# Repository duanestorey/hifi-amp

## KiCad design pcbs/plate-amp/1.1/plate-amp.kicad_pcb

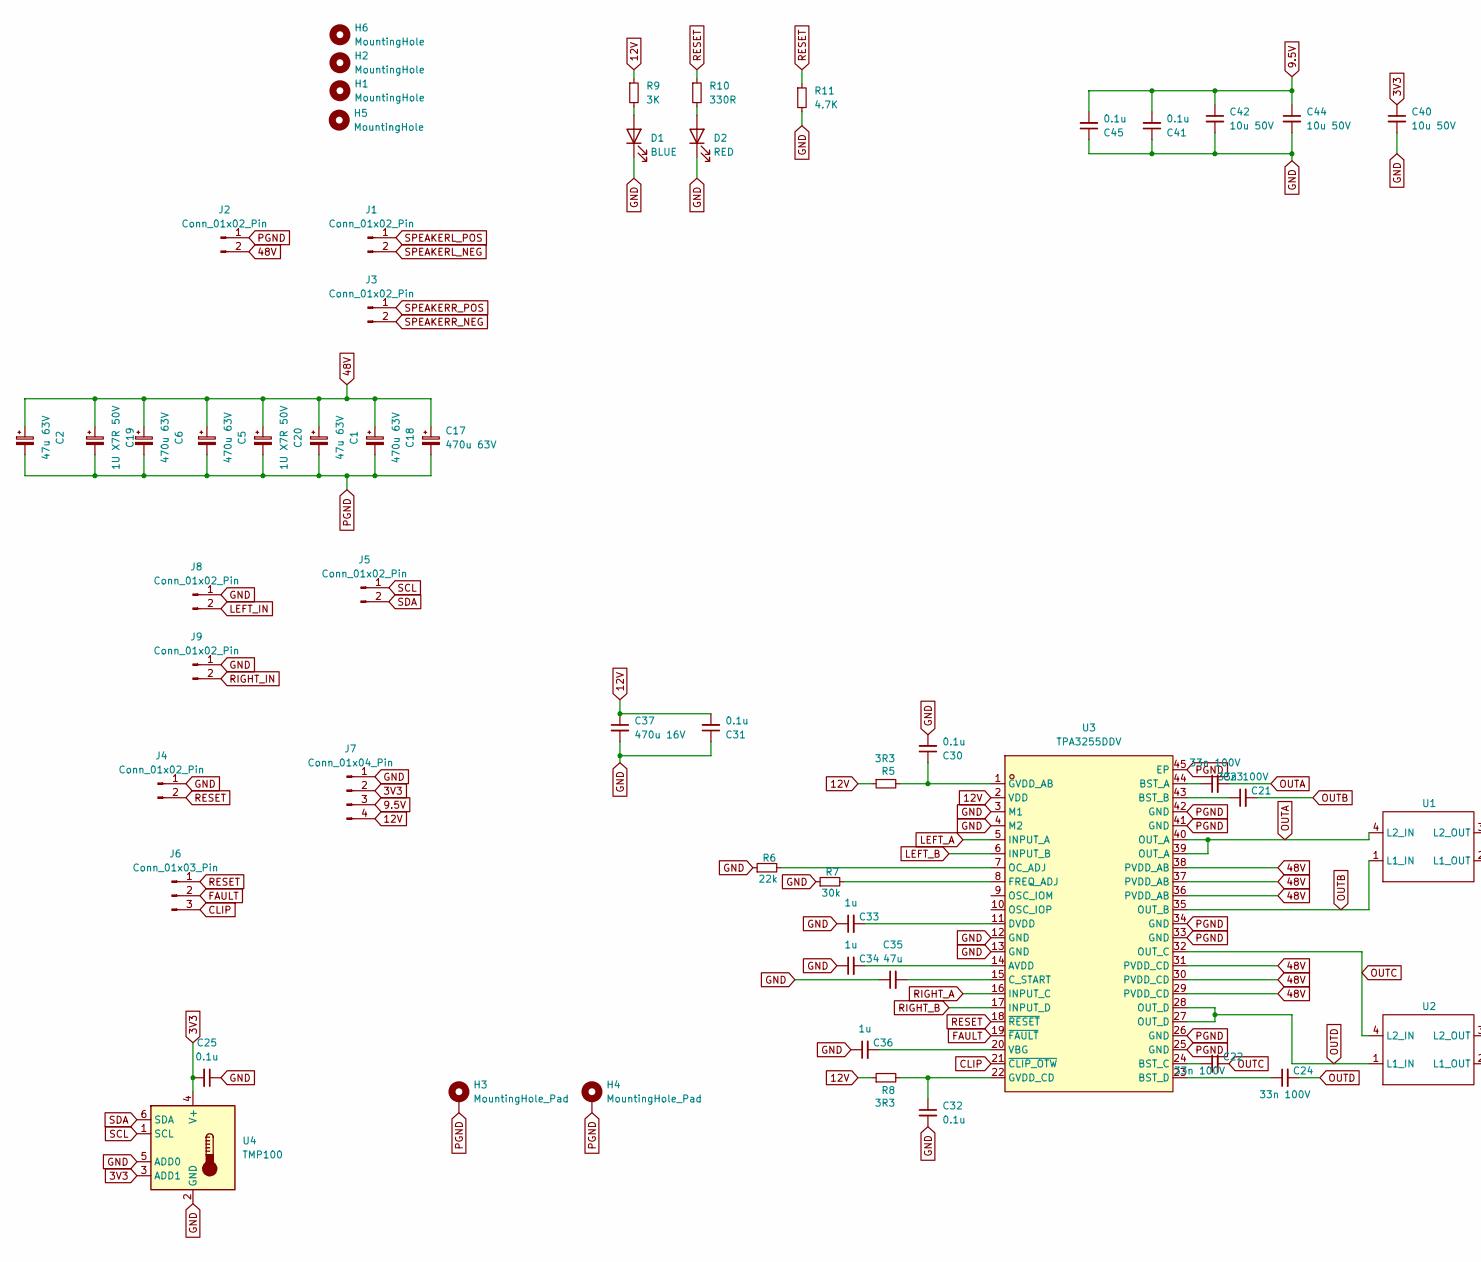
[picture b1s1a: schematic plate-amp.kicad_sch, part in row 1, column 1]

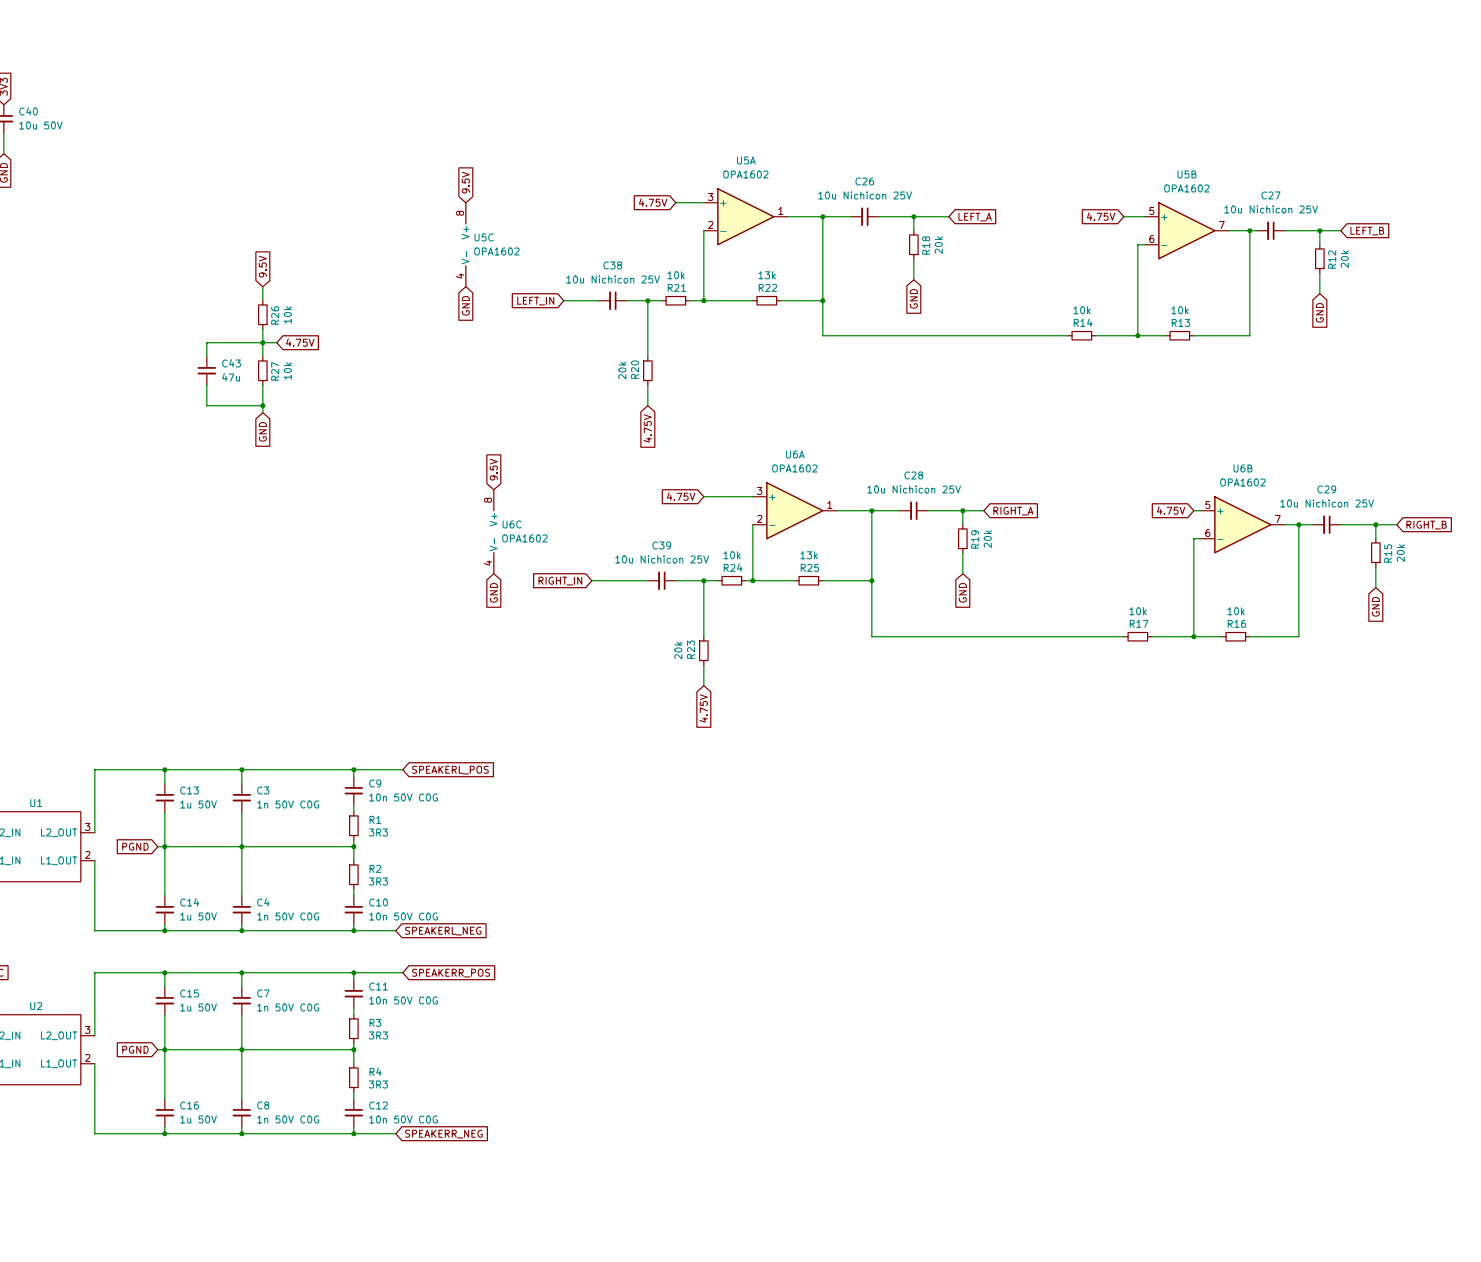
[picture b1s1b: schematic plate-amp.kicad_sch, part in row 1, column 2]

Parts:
C1, C2: 47u 63V; CP_Radial_D6.3mm_P2.50mm; LCSC C45673
C3, C4, C7, C8: 1n 50V C0G; C_1206_3216Metric_Pad1.33x1.80mm_HandSolder
C5, C6, C17, C18: 470u 63V; CP_Radial_D13.0mm_P5.00mm; LCSC C18823
C9, C10, C11, C12: 10n 50V C0G; C_1206_3216Metric_Pad1.33x1.80mm_HandSolder
C13, C14, C15, C16: 1u 50V; CP_Radial_D5.0mm_P2.00mm
C19, C20: 1U X7R 50V; C_1206_3216Metric_Pad1.33x1.80mm_HandSolder; Mouser 80-C1206X475J5RACTU
C21, C22, C23, C24: 33n 100V; C_1206_3216Metric_Pad1.33x1.80mm_HandSolder
C25, C30, C31, C32, C41, C45: 0.1u; C_0805_2012Metric_Pad1.18x1.45mm_HandSolder
C26, C27, C28, C29, C38, C39: 10u Nichicon 25V; CP_Radial_D5.0mm_P2.50mm
C33, C34, C36: 1u; C_1206_3216Metric_Pad1.33x1.80mm_HandSolder
C35, C43: 47u; C_1206_3216Metric_Pad1.33x1.80mm_HandSolder
C37: 470u 16V; CP_Radial_D8.0mm_P3.50mm
C40, C42, C44: 10u 50V; C_1206_3216Metric_Pad1.33x1.80mm_HandSolder
D1: BLUE; LED_0603_1608Metric_Pad1.05x0.95mm_HandSolder; LCSC XL-1608UBC-04
D2: RED; LED_0603_1608Metric_Pad1.05x0.95mm_HandSolder; LCSC XL-1608UBC-04
H1, H2, H5, H6: MountingHole; MountingHole_3.2mm_M3_DIN965_Pad_TopOnly
H3, H4: MountingHole_Pad; MountingHole_3.2mm_M3_DIN965_Pad_TopBottom
J1, J2, J3: Conn_01x02_Pin; TerminalBlock_MaiXu_MX126-5.0-02P_1x02_P5.00mm
J4, J5, J8, J9: Conn_01x02_Pin; JST_PH_B2B-PH-K_1x02_P2.00mm_Vertical
J6: Conn_01x03_Pin; JST_PH_B3B-PH-K_1x03_P2.00mm_Vertical
J7: Conn_01x04_Pin; JST_PH_B4B-PH-K_1x04_P2.00mm_Vertical
R1, R2, R3, R4: 3R3; R_2512_6332Metric_Pad1.40x3.35mm_HandSolder
R5, R8: 3R3; C_0603_1608Metric_Pad1.08x0.95mm_HandSolder
R6: 22k; C_0603_1608Metric_Pad1.08x0.95mm_HandSolder
R7: 30k; C_0603_1608Metric_Pad1.08x0.95mm_HandSolder
R9: 3K; R_0603_1608Metric_Pad0.98x0.95mm_HandSolder
R10: 330R; R_0603_1608Metric_Pad0.98x0.95mm_HandSolder
R11: 4.7K; R_0603_1608Metric_Pad0.98x0.95mm_HandSolder
R12, R15, R18, R19, R20, R23: 20k; C_0603_1608Metric_Pad1.08x0.95mm_HandSolder
R13, R14, R16, R17, R21, R24, R26, R27: 10k; C_0603_1608Metric_Pad1.08x0.95mm_HandSolder
R22, R25: 13k; C_0603_1608Metric_Pad1.08x0.95mm_HandSolder
U1, U2: UA8014-AL
U3: TPA3255DDV; HTSSOP-44_L14.0-W6.1-P0.64-LS8.1-BL-EP; LCSC Part C468240
U4: TMP100; SOT-23-6
U5, U6: OPA1602; SOIC-8_3.9x4.9mm_P1.27mm

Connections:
3V3: C25.2, C40.1, J7.2, U4.3 (ADD1), U4.4 (V+)
4.75V: C43.1, R20.2, R23.2, R26.1, R27.2, U5.3 (+), U5.5 (+), U6.3 (+), U6.5 (+)
9.5V: C41.2, C42.1, C44.1, C45.2, J7.3, R26.2, U5.8 (V+), U6.8 (V+)
12V: C31.2, C37.1, J7.4, R5.1, R8.1, R9.1, U3.2 (VDD)
48V: C1.1, C2.1, C5.1, C6.1, C17.1, C18.1, C19.1, C20.1, J2.2, U3.29 (PVDD_CD), U3.30 (PVDD_CD), U3.31 (PVDD_CD), U3.36 (PVDD_AB), U3.37 (PVDD_AB), U3.38 (PVDD_AB)
CLIP: J6.3, U3.21 (~CLIP_OTW)
FAULT: J6.2, U3.19 (~FAULT)
GND: C25.1, C30.2, C31.1, C32.2, C33.1, C34.1, C35.1, C36.1, C37.2, C40.2, C41.1, C42.2, C43.2, C44.2, C45.1, D1.1 (K), D2.1 (K), J4.1, J7.1, J8.1, J9.1, R6.1, R7.1, R11.2, R12.1, R15.1, R18.1, R19.1, R27.1, U3.3 (M1), U3.4 (M2), U3.12 (GND), U3.13 (GND), U4.2 (GND), U4.5 (ADD0), U5.4 (V-), U6.4 (V-)
LEFT_A: C26.1, R18.2, U3.5 (INPUT_A)
LEFT_B: C27.1, R12.2, U3.6 (INPUT_B)
LEFT_IN: C38.2, J8.2
unnamed: C9.2, R1.1
unnamed: C10.1, R2.2
unnamed: C11.2, R3.1
unnamed: C12.1, R4.2
unnamed: C26.2, R14.2, R22.1, U5.1
unnamed: C27.2, R13.1, U5.7
unnamed: C28.2, R17.2, R25.1, U6.1
unnamed: C29.2, R16.1, U6.7
unnamed: C38.1, R20.1, R21.2
unnamed: C39.1, R23.1, R24.2
unnamed: D1.2 (A), R9.2
unnamed: D2.2 (A), R10.2
unnamed: C34.2, U3.14 (AVDD)
unnamed: C23.1, U3.44 (BST_A)
unnamed: C21.1, U3.43 (BST_B)
unnamed: C22.1, U3.24 (BST_C)
unnamed: C24.1, U3.23 (BST_D)
unnamed: C35.2, U3.15 (C_START)
unnamed: C33.2, U3.11 (DVDD)
unnamed: R7.2, U3.8 (FREQ_ADJ)
unnamed: C30.1, R5.2, U3.1 (GVDD_AB)
unnamed: C32.1, R8.2, U3.22 (GVDD_CD)
unnamed: R6.2, U3.7 (OC_ADJ)
unnamed: C36.2, U3.20 (VBG)
unnamed: R21.1, R22.2, U5.2 (-)
unnamed: R13.2, R14.1, U5.6 (-)
unnamed: R24.1, R25.2, U6.2 (-)
unnamed: R16.2, R17.1, U6.6 (-)
OUTA: C23.2, U1.4 (L2_IN), U3.39 (OUT_A), U3.40 (OUT_A)
OUTB: C21.2, U1.1 (L1_IN), U3.35 (OUT_B)
OUTC: C22.2, U2.4 (L2_IN), U3.32 (OUT_C)
OUTD: C24.2, U2.1 (L1_IN), U3.27 (OUT_D), U3.28 (OUT_D)
PGND: C1.2, C2.2, C3.2, C4.1, C5.2, C6.2, C7.2, C8.1, C13.2, C14.1, C15.2, C16.1, C17.2, C18.2, C19.2, C20.2, H3.1, H4.1, J2.1, R1.2, R2.1, R3.2, R4.1, U3.25 (GND), U3.26 (GND), U3.33 (GND), U3.34 (GND), U3.41 (GND), U3.42 (GND), U3.45 (EP)
RESET: J4.2, J6.1, R10.1, R11.1, U3.18 (~RESET)
RIGHT_A: C28.1, R19.2, U3.16 (INPUT_C)
RIGHT_B: C29.1, R15.2, U3.17 (INPUT_D)
RIGHT_IN: C39.2, J9.2
SCL: J5.1, U4.1 (SCL)
SDA: J5.2, U4.6 (SDA)
SPEAKERL_NEG: C4.2, C10.2, C14.2, J1.2, U1.2 (L1_OUT)
SPEAKERL_POS: C3.1, C9.1, C13.1, J1.1, U1.3 (L2_OUT)
SPEAKERR_NEG: C8.2, C12.2, C16.2, J3.2, U2.2 (L1_OUT)
SPEAKERR_POS: C7.1, C11.1, C15.1, J3.1, U2.3 (L2_OUT)

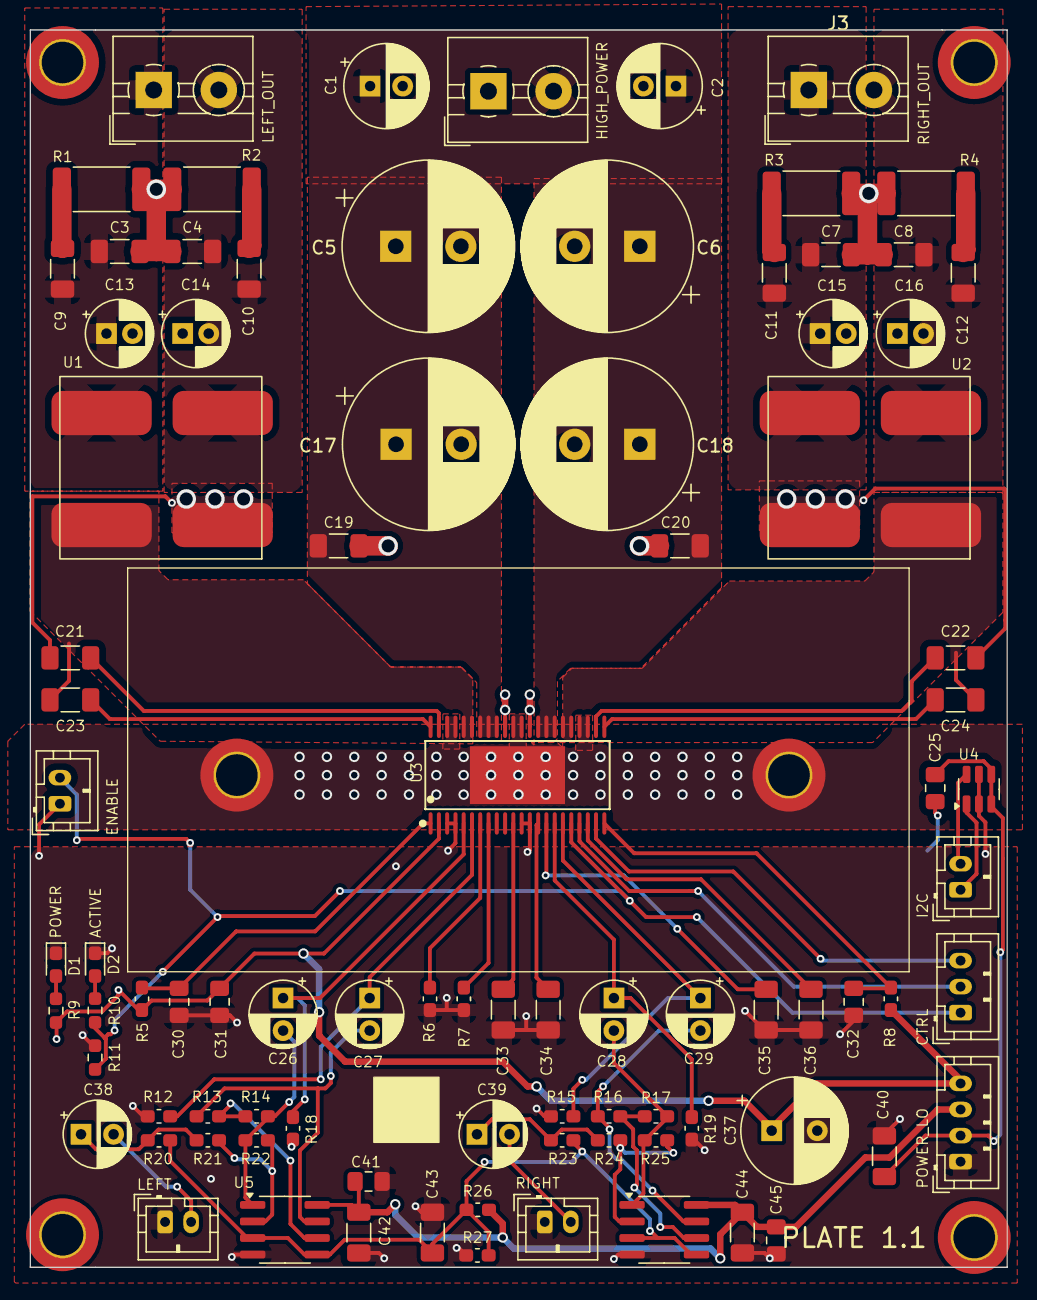
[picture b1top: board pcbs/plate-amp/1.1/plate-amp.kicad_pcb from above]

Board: 2 copper layers, 75.0 x 95.0 mm, 95 parts (0 on the bottom side), 54 nets.

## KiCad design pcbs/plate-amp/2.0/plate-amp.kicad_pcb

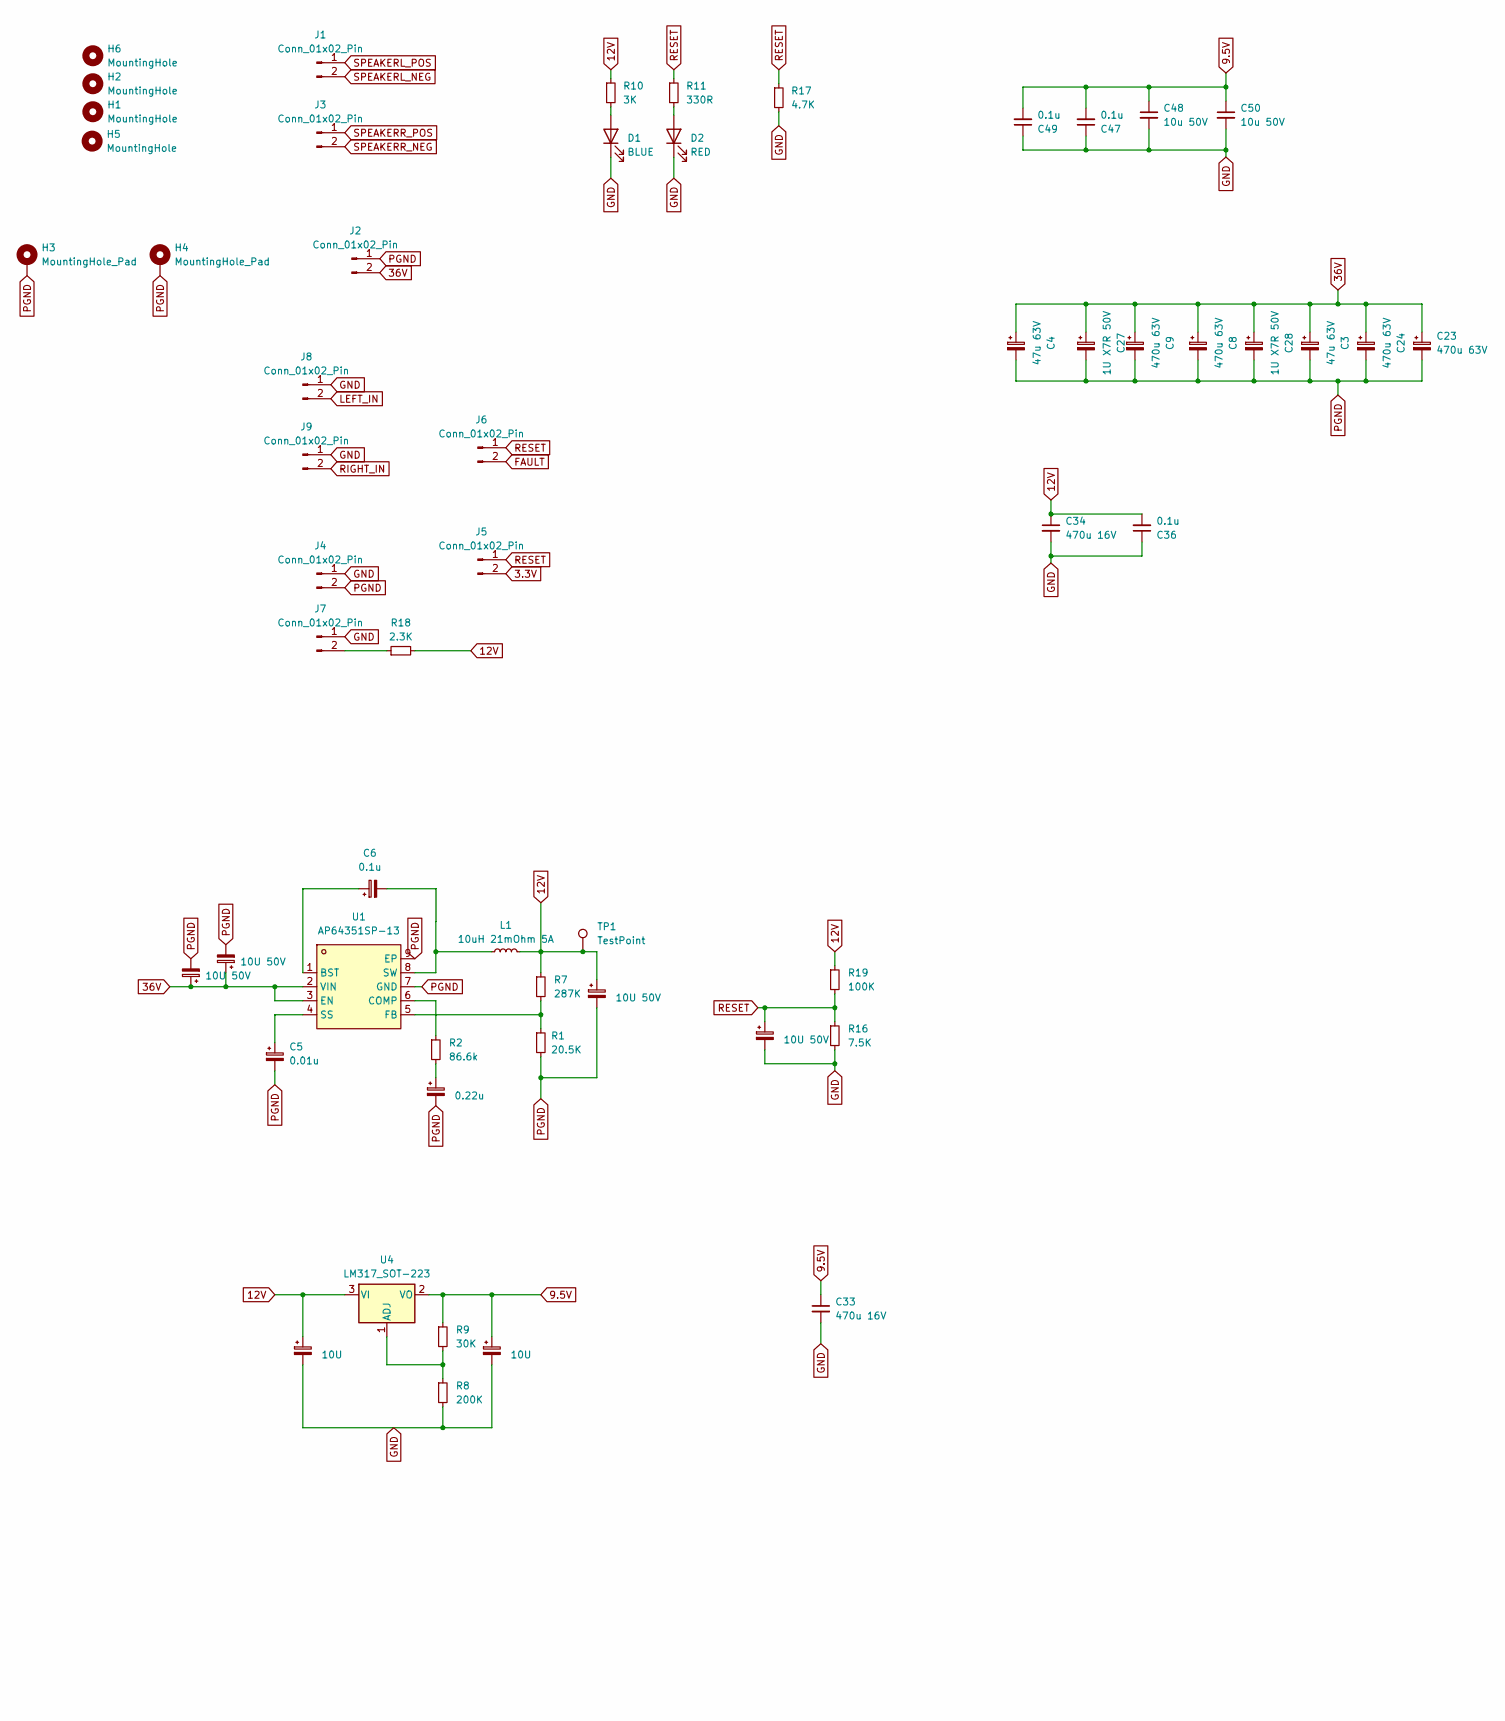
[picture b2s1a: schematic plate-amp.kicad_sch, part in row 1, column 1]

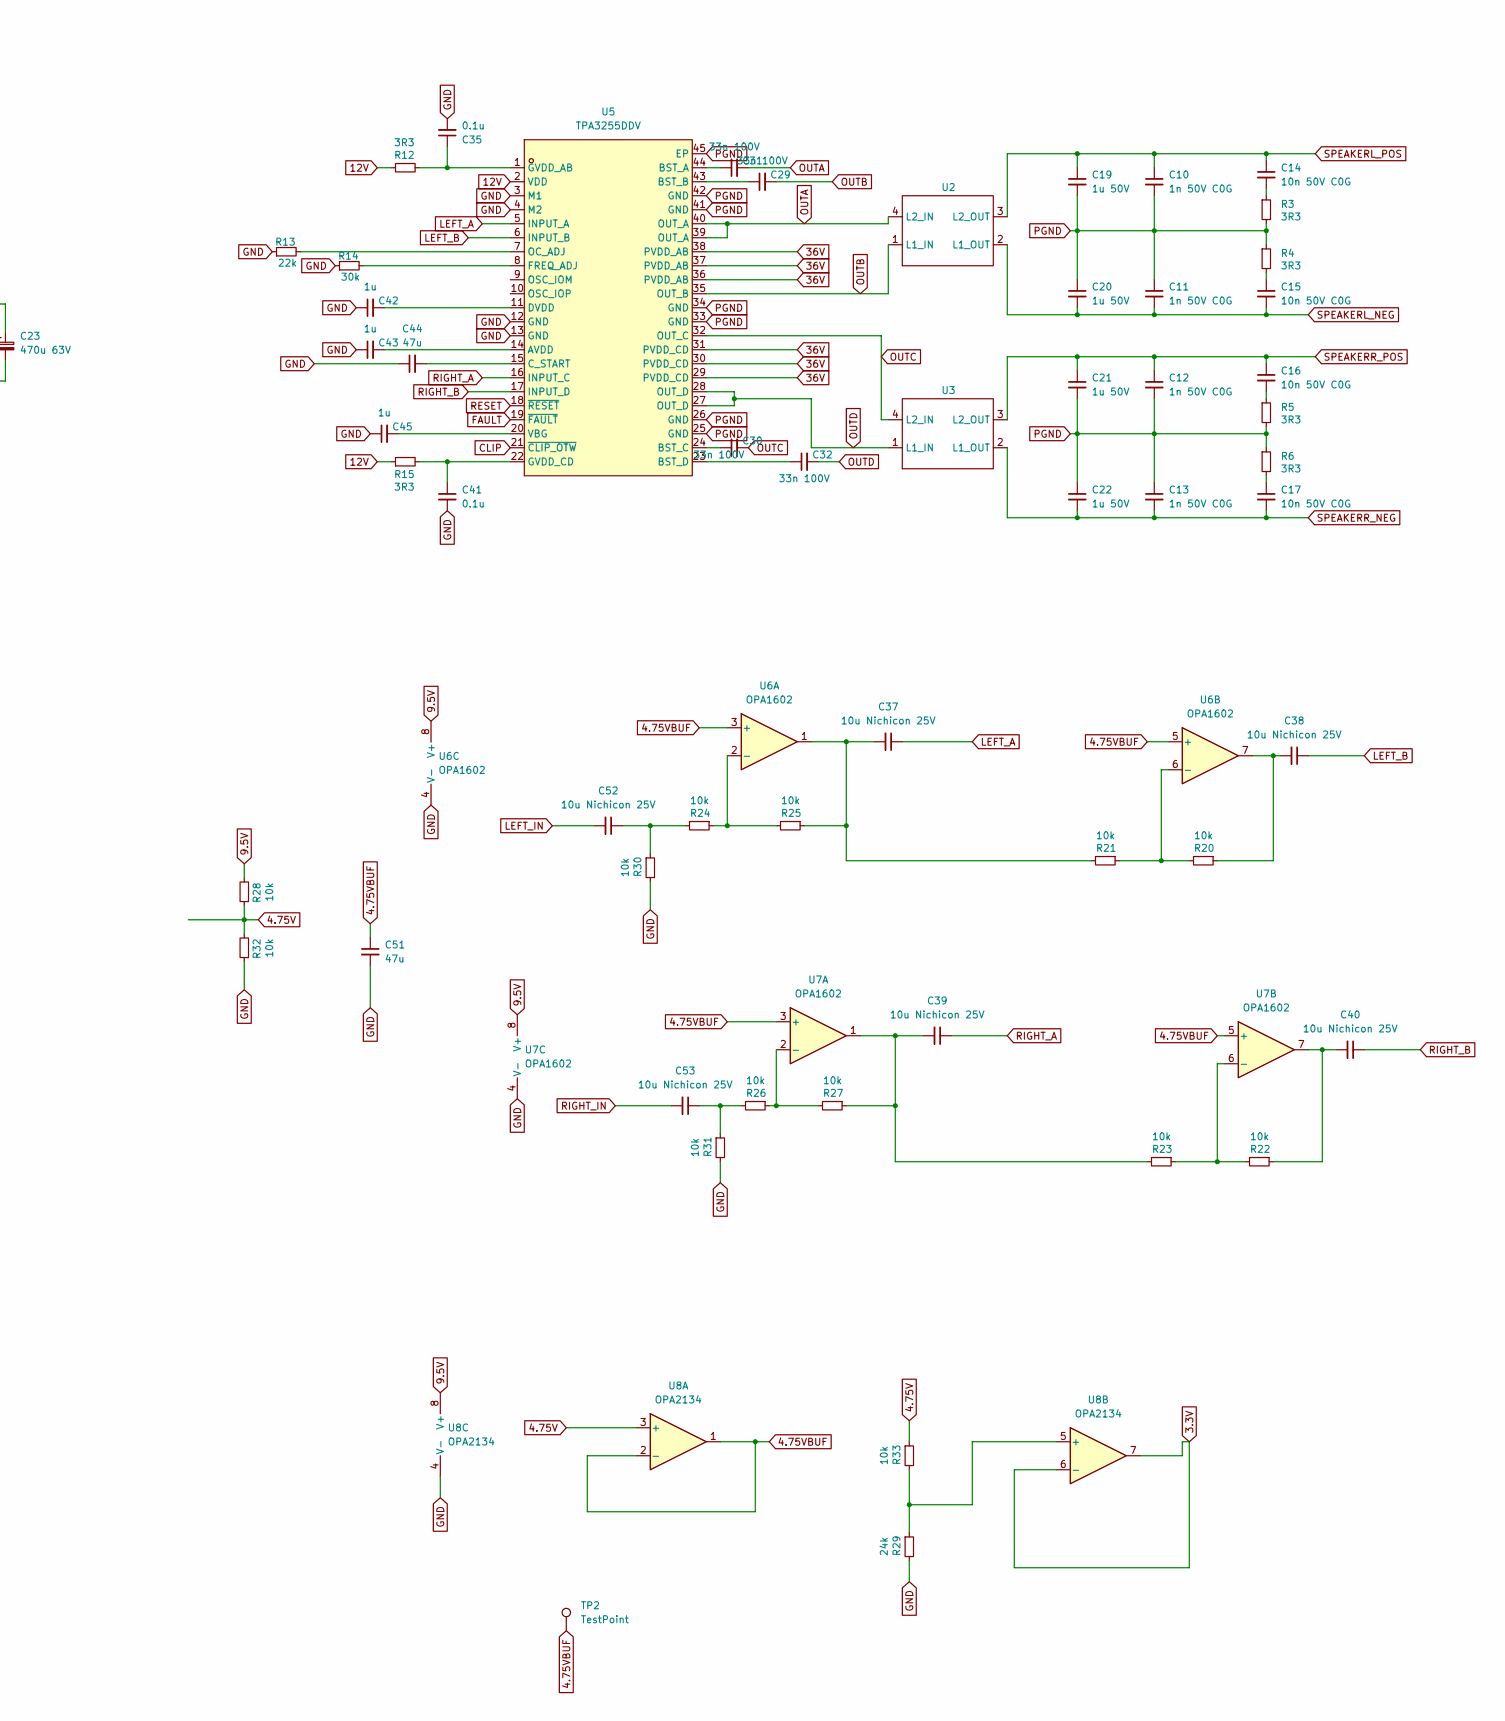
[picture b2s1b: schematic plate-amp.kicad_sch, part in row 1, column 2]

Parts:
C1, C2, C18, C46: 10U 50V; C_1206_3216Metric_Pad1.33x1.80mm_HandSolder
C3, C4: 47u 63V; CP_Radial_D6.3mm_P2.50mm; LCSC C45673
C5: 0.01u; C_0805_2012Metric_Pad1.18x1.45mm_HandSolder
C6, C35, C36, C41, C47, C49: 0.1u; C_0805_2012Metric_Pad1.18x1.45mm_HandSolder
C7: 0.22u; C_0805_2012Metric_Pad1.18x1.45mm_HandSolder
C8, C9, C23, C24: 470u 63V; CP_Radial_D13.0mm_P5.00mm; LCSC C18823
C10, C11, C12, C13: 1n 50V C0G; C_1206_3216Metric_Pad1.33x1.80mm_HandSolder
C14, C15, C16, C17: 10n 50V C0G; C_1206_3216Metric_Pad1.33x1.80mm_HandSolder
C19, C20, C21, C22: 1u 50V; CP_Radial_D5.0mm_P2.00mm
C25, C26: 10U; C_1206_3216Metric_Pad1.33x1.80mm_HandSolder
C27, C28: 1U X7R 50V; C_1206_3216Metric_Pad1.33x1.80mm_HandSolder; Mouser 80-C1206X475J5RACTU
C29, C30, C31, C32: 33n 100V; C_1206_3216Metric_Pad1.33x1.80mm_HandSolder
C33, C34: 470u 16V; CP_Radial_D8.0mm_P3.50mm
C37, C38, C39, C40, C52, C53: 10u Nichicon 25V; CP_Radial_D5.0mm_P2.50mm
C42, C43, C45: 1u; C_1206_3216Metric_Pad1.33x1.80mm_HandSolder
C44, C51: 47u; C_1206_3216Metric_Pad1.33x1.80mm_HandSolder
C48, C50: 10u 50V; C_1206_3216Metric_Pad1.33x1.80mm_HandSolder
D1: BLUE; LED_0603_1608Metric_Pad1.05x0.95mm_HandSolder; LCSC XL-1608UBC-04
D2: RED; LED_0603_1608Metric_Pad1.05x0.95mm_HandSolder; LCSC XL-1608UBC-04
H1, H2, H5, H6: MountingHole; MountingHole_3.2mm_M3_DIN965_Pad_TopOnly
H3, H4: MountingHole_Pad; MountingHole_3.2mm_M3_DIN965_Pad_TopBottom
J1, J2, J3: Conn_01x02_Pin; TerminalBlock_MaiXu_MX126-5.0-02P_1x02_P5.00mm
J4, J5: Conn_01x02_Pin; PinHeader_1x02_P2.54mm_Vertical
J6, J7, J8, J9: Conn_01x02_Pin; JST_PH_B2B-PH-K_1x02_P2.00mm_Vertical
L1: 10uH 21mOhm 5A; L_Vishay_IHLP-4040; Mouser 704-DR1040-7R0-R
R1: 20.5K; R_0603_1608Metric_Pad0.98x0.95mm_HandSolder; Mouser 603-RC0603JR-07820KP
R2: 86.6k; R_0603_1608Metric_Pad0.98x0.95mm_HandSolder; Mouser 71-CRCW0603-86.6K-E3
R3, R4, R5, R6: 3R3; R_2512_6332Metric_Pad1.40x3.35mm_HandSolder
R7: 287K; R_0603_1608Metric_Pad0.98x0.95mm_HandSolder; Mouser 603-RC0603JR-10180KL
R8: 200K; R_0603_1608Metric_Pad0.98x0.95mm_HandSolder
R9: 30K; R_0603_1608Metric_Pad0.98x0.95mm_HandSolder
R10: 3K; R_0603_1608Metric_Pad0.98x0.95mm_HandSolder
R11: 330R; R_0603_1608Metric_Pad0.98x0.95mm_HandSolder
R12, R15: 3R3; C_0603_1608Metric_Pad1.08x0.95mm_HandSolder
R13: 22k; C_0603_1608Metric_Pad1.08x0.95mm_HandSolder
R14: 30k; C_0603_1608Metric_Pad1.08x0.95mm_HandSolder
R16: 7.5K; R_0603_1608Metric_Pad0.98x0.95mm_HandSolder; Mouser 603-RC0603JR-10180KL
R17: 4.7K; R_0603_1608Metric_Pad0.98x0.95mm_HandSolder
R18: 2.3K; R_0603_1608Metric_Pad0.98x0.95mm_HandSolder; Mouser 603-RC0603JR-10180KL
R19: 100K; R_0603_1608Metric_Pad0.98x0.95mm_HandSolder; Mouser 603-RC0603JR-10180KL
R20, R21, R22, R23, R24, R25, R26, R27, R28, R30, R31, R32, R33: 10k; C_0603_1608Metric_Pad1.08x0.95mm_HandSolder
R29: 24k; C_0603_1608Metric_Pad1.08x0.95mm_HandSolder
TP1: TestPoint; TestPoint_THTPad_D2.0mm_Drill1.0mm
TP2: TestPoint; TestPoint_THTPad_2.5x2.5mm_Drill1.2mm
U1: AP64351SP-13; SOIC-8_L4.9-W3.9-P1.27-LS6.0-BL-EP; LCSC Part C3192339
U2, U3: UA8014-AL
U4: LM317_SOT-223; SOT-223-3_TabPin2
U5: TPA3255DDV; HTSSOP-44_L14.0-W6.1-P0.64-LS8.1-BL-EP; LCSC Part C468240
U6, U7: OPA1602; DIP-8_W7.62mm
U8: OPA2134; SOIC-8_3.9x4.9mm_P1.27mm

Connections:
3.3V: J5.2, U8.6 (-), U8.7
4.75V: R28.1, R32.2, R33.1, U8.3 (+)
4.75VBUF: C51.1, TP2.1, U6.3 (+), U6.5 (+), U7.3 (+), U7.5 (+), U8.1, U8.2 (-)
9.5V: C26.1, C33.1, C47.2, C48.1, C49.2, C50.1, R9.1, R28.2, U4.2 (VO), U6.8 (V+), U7.8 (V+), U8.8 (V+)
12V: C18.1, C25.1, C34.1, C36.2, L1.2, R7.1, R10.1, R12.1, R15.1, R18.2, R19.1, TP1.1, U4.3 (VI), U5.2 (VDD)
36V: C1.1, C2.1, C3.1, C4.1, C8.1, C9.1, C23.1, C24.1, C27.1, C28.1, J2.2, U1.2 (VIN), U1.3 (EN), U5.29 (PVDD_CD), U5.30 (PVDD_CD), U5.31 (PVDD_CD), U5.36 (PVDD_AB), U5.37 (PVDD_AB), U5.38 (PVDD_AB)
CLIP: U5.21 (~CLIP_OTW)
FAULT: J6.2, U5.19 (~FAULT)
GND: C25.2, C26.2, C33.2, C34.2, C35.2, C36.1, C41.2, C42.1, C43.1, C44.1, C45.1, C46.2, C47.1, C48.2, C49.1, C50.2, C51.2, D1.1 (K), D2.1 (K), J4.1, J7.1, J8.1, J9.1, R8.2, R13.1, R14.1, R16.2, R17.2, R29.2, R30.2, R31.2, R32.1, U5.3 (M1), U5.4 (M2), U5.12 (GND), U5.13 (GND), U6.4 (V-), U7.4 (V-), U8.4 (V-)
LEFT_A: C37.1, U5.5 (INPUT_A)
LEFT_B: C38.1, U5.6 (INPUT_B)
LEFT_IN: C52.2, J8.2
unnamed: C7.1, R2.2
unnamed: C14.2, R3.1
unnamed: C15.1, R4.2
unnamed: C16.2, R5.1
unnamed: C17.1, R6.2
unnamed: C37.2, R21.2, R25.1, U6.1
unnamed: C38.2, R20.1, U6.7
unnamed: C39.2, R23.2, R27.1, U7.1
unnamed: C40.2, R22.1, U7.7
unnamed: C52.1, R24.2, R30.1
unnamed: C53.1, R26.2, R31.1
unnamed: D1.2 (A), R10.2
unnamed: D2.2 (A), R11.2
unnamed: J7.2, R18.1
unnamed: C6.1, U1.1 (BST)
unnamed: R2.1, U1.6 (COMP)
unnamed: R1.1, R7.2, U1.5 (FB)
unnamed: C5.1, U1.4 (SS)
unnamed: C6.2, L1.1, U1.8 (SW)
unnamed: R8.1, R9.2, U4.1 (ADJ)
unnamed: C43.2, U5.14 (AVDD)
unnamed: C31.1, U5.44 (BST_A)
unnamed: C29.1, U5.43 (BST_B)
unnamed: C30.1, U5.24 (BST_C)
unnamed: C32.1, U5.23 (BST_D)
unnamed: C44.2, U5.15 (C_START)
unnamed: C42.2, U5.11 (DVDD)
unnamed: R14.2, U5.8 (FREQ_ADJ)
unnamed: C35.1, R12.2, U5.1 (GVDD_AB)
unnamed: C41.1, R15.2, U5.22 (GVDD_CD)
unnamed: R13.2, U5.7 (OC_ADJ)
unnamed: C45.2, U5.20 (VBG)
unnamed: R24.1, R25.2, U6.2 (-)
unnamed: R20.2, R21.1, U6.6 (-)
unnamed: R26.1, R27.2, U7.2 (-)
unnamed: R22.2, R23.1, U7.6 (-)
unnamed: R29.1, R33.2, U8.5 (+)
OUTA: C31.2, U2.4 (L2_IN), U5.39 (OUT_A), U5.40 (OUT_A)
OUTB: C29.2, U2.1 (L1_IN), U5.35 (OUT_B)
OUTC: C30.2, U3.4 (L2_IN), U5.32 (OUT_C)
OUTD: C32.2, U3.1 (L1_IN), U5.27 (OUT_D), U5.28 (OUT_D)
PGND: C1.2, C2.2, C3.2, C4.2, C5.2, C7.2, C8.2, C9.2, C10.2, C11.1, C12.2, C13.1, C18.2, C19.2, C20.1, C21.2, C22.1, C23.2, C24.2, C27.2, C28.2, H3.1, H4.1, J2.1, J4.2, R1.2, R3.2, R4.1, R5.2, R6.1, U1.7 (GND), U1.9 (EP), U5.25 (GND), U5.26 (GND), U5.33 (GND), U5.34 (GND), U5.41 (GND), U5.42 (GND), U5.45 (EP)
RESET: C46.1, J5.1, J6.1, R11.1, R16.1, R17.1, R19.2, U5.18 (~RESET)
RIGHT_A: C39.1, U5.16 (INPUT_C)
RIGHT_B: C40.1, U5.17 (INPUT_D)
RIGHT_IN: C53.2, J9.2
SPEAKERL_NEG: C11.2, C15.2, C20.2, J1.2, U2.2 (L1_OUT)
SPEAKERL_POS: C10.1, C14.1, C19.1, J1.1, U2.3 (L2_OUT)
SPEAKERR_NEG: C13.2, C17.2, C22.2, J3.2, U3.2 (L1_OUT)
SPEAKERR_POS: C12.1, C16.1, C21.1, J3.1, U3.3 (L2_OUT)

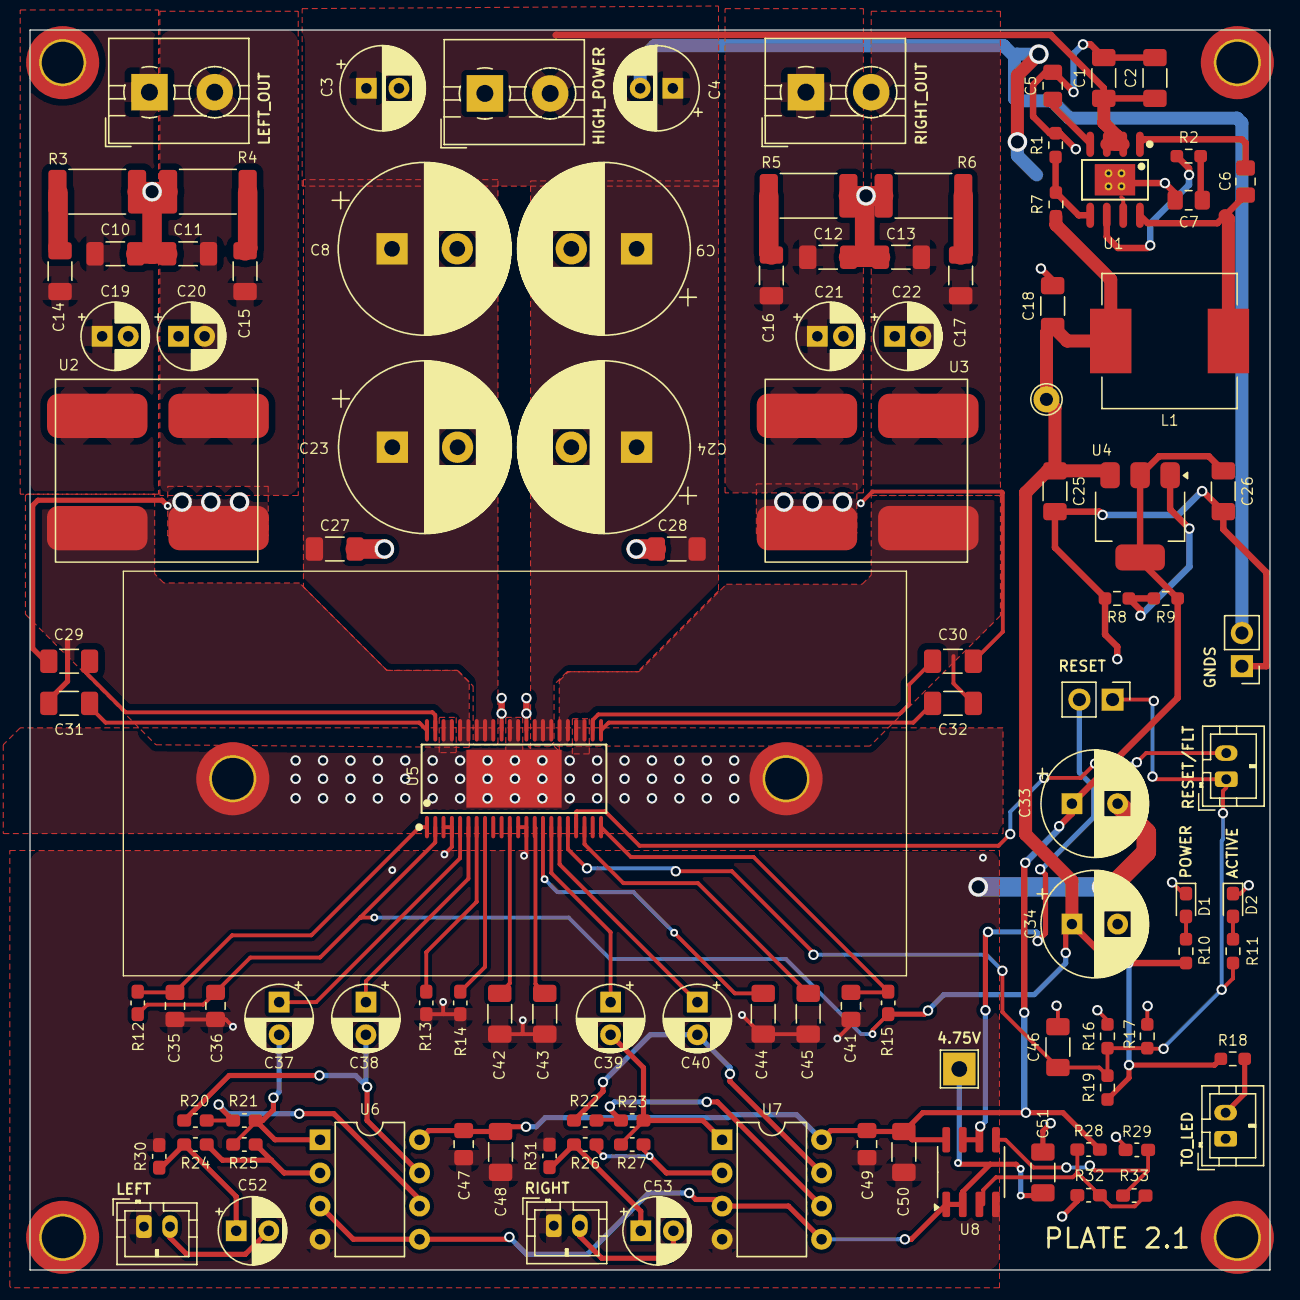
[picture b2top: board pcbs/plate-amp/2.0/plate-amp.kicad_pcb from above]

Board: 2 copper layers, 95.0 x 95.0 mm, 114 parts (0 on the bottom side), 61 nets.

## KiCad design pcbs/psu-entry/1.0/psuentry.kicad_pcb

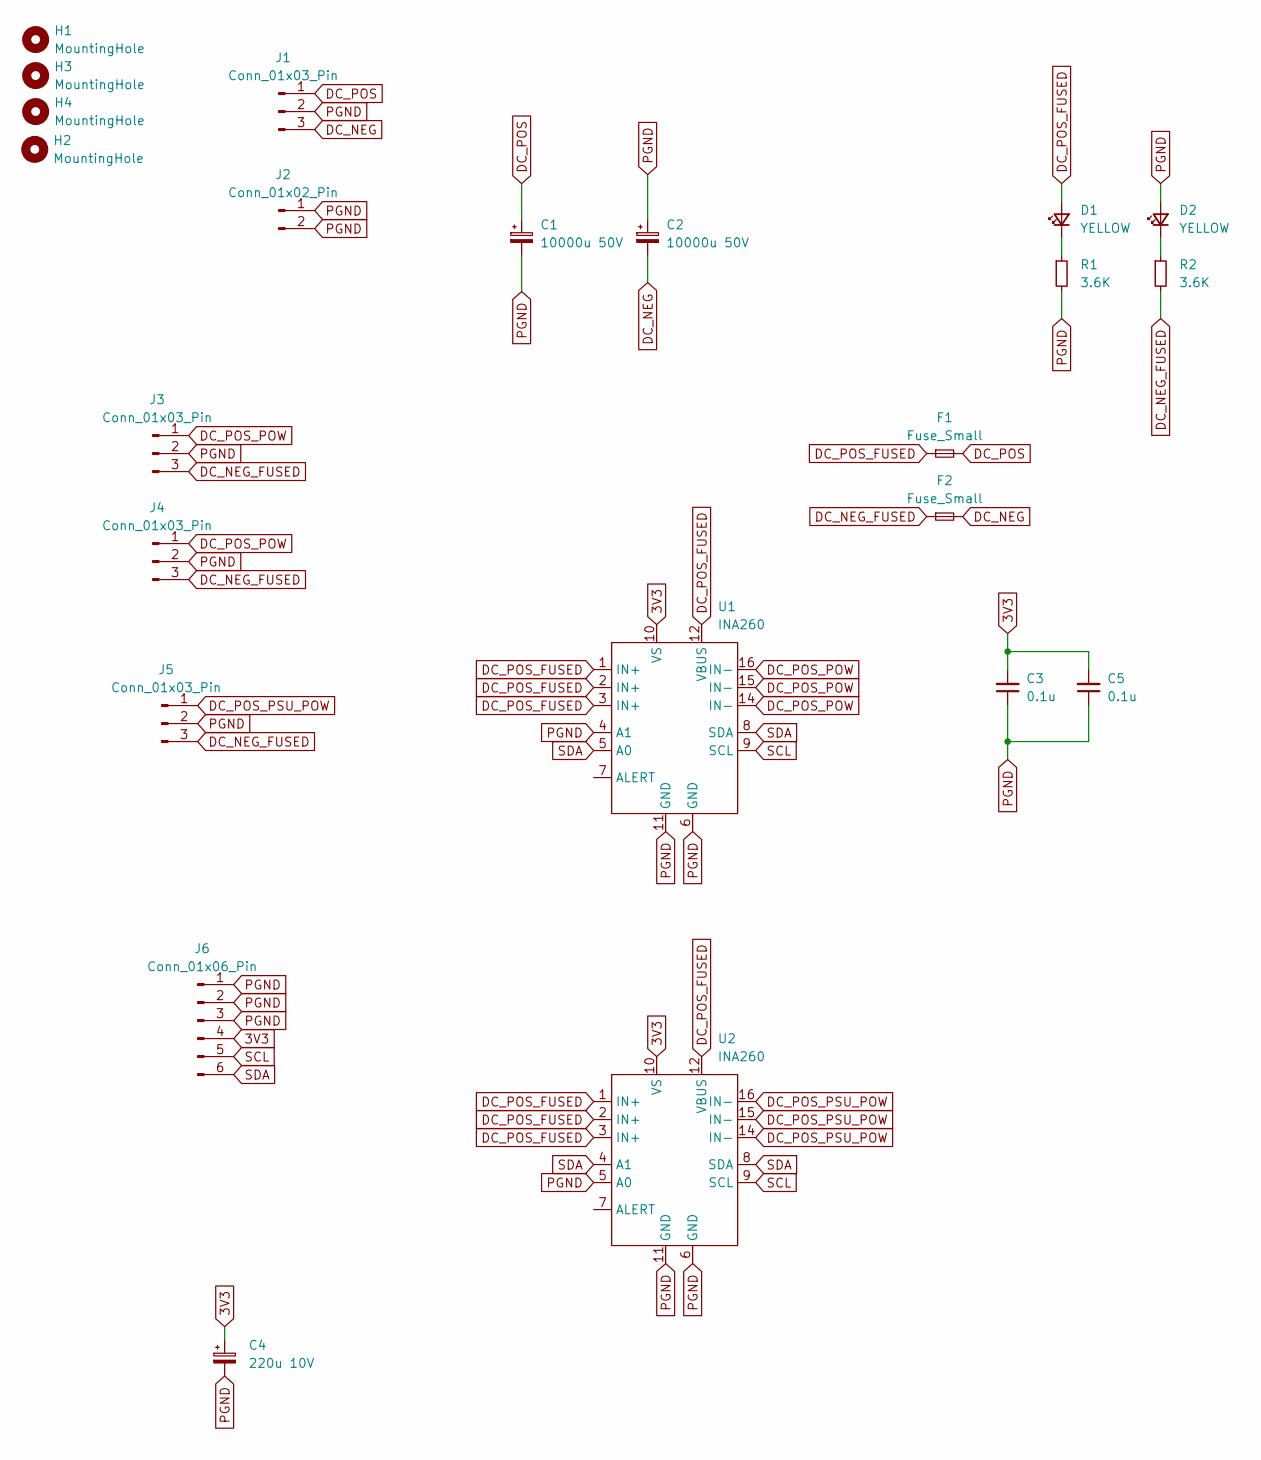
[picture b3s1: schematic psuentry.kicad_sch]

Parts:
C1, C2: 10000u 50V; CP_Radial_D25.0mm_P10.00mm_SnapIn
C3, C5: 0.1u; C_0805_2012Metric_Pad1.18x1.45mm_HandSolder
C4: 220u 10V; CP_Radial_D6.3mm_P2.50mm
D1, D2: YELLOW; LED_0805_2012Metric_Pad1.15x1.40mm_HandSolder
F1, F2: Fuse_Small; Aliexpress Fuse 5x20
H1, H2, H3, H4: MountingHole; MountingHole_3.2mm_M3_DIN965_Pad_TopOnly
J1, J3, J4, J5: Conn_01x03_Pin; JST_VH_B3P-VH-B_1x03_P3.96mm_Vertical
J2: Conn_01x02_Pin; JST_VH_B2P-VH-B_1x02_P3.96mm_Vertical
J6: Conn_01x06_Pin; JST_PH_B6B-PH-K_1x06_P2.00mm_Vertical
R1, R2: 3.6K; R_0603_1608Metric_Pad0.98x0.95mm_HandSolder
U1, U2: INA260; TSSOP-16_4.4x5mm_P0.65mm

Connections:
3V3: C3.2, C4.1, C5.2, J6.4, U1.10 (VS), U2.10 (VS)
DC_NEG: C2.2, F2.2, J1.3
DC_NEG_FUSED: F2.1, J3.3, J4.3, J5.3, R2.2
DC_POS: C1.1, F1.2, J1.1
DC_POS_FUSED: D1.2 (A), F1.1, U1.1 (IN+), U1.2 (IN+), U1.3 (IN+), U1.12 (VBUS), U2.1 (IN+), U2.2 (IN+), U2.3 (IN+), U2.12 (VBUS)
DC_POS_POW: J3.1, J4.1, U1.14 (IN-), U1.15 (IN-), U1.16 (IN-)
DC_POS_PSU_POW: J5.1, U2.14 (IN-), U2.15 (IN-), U2.16 (IN-)
unnamed: D1.1 (K), R1.1
unnamed: D2.1 (K), R2.1
PGND: C1.2, C2.1, C3.1, C4.2, C5.1, D2.2 (A), J1.2, J2.1, J2.2, J3.2, J4.2, J5.2, J6.1, J6.2, J6.3, R1.2, U1.4 (A1), U1.6 (GND), U1.11 (GND), U2.5 (A0), U2.6 (GND), U2.11 (GND)
SCL: J6.5, U1.9 (SCL), U2.9 (SCL)
SDA: J6.6, U1.5 (A0), U1.8 (SDA), U2.4 (A1), U2.8 (SDA)

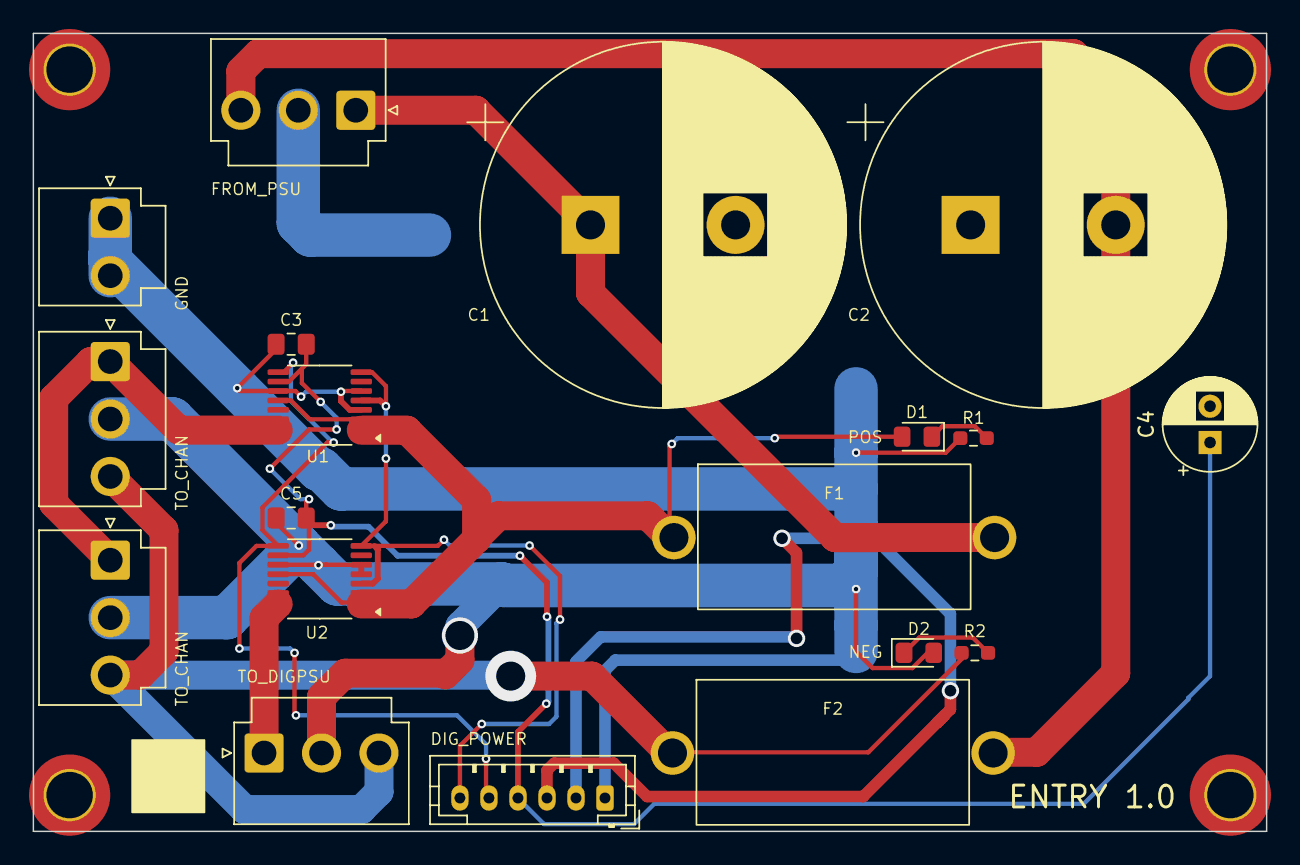
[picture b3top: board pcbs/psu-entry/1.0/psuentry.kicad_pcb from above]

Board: 2 copper layers, 85.0 x 55.0 mm, 23 parts (0 on the bottom side), 12 nets.
